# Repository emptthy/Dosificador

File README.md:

Este proyecto consta de una base de varillas y rulemanes, que servirán como soporte para una jeringa, la cual contendrá el líquido que queramos inyectar, para luego ser empujada por un motor paso a paso al marcar en un teclado la cantidad de la dosis solicitada.

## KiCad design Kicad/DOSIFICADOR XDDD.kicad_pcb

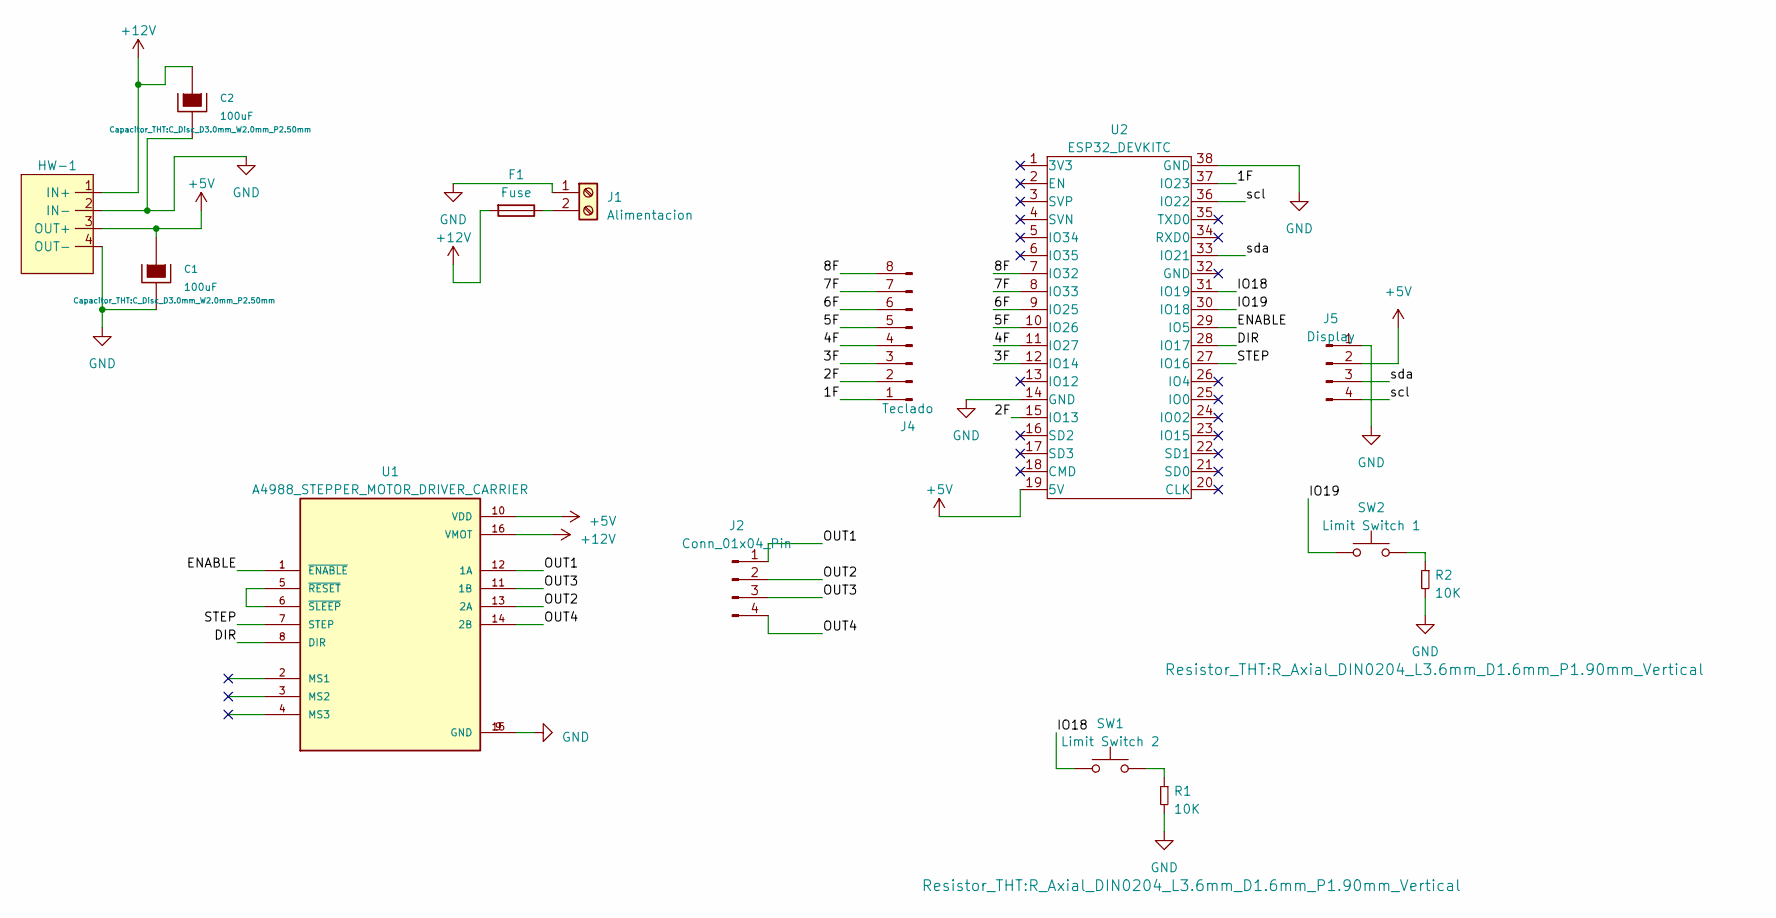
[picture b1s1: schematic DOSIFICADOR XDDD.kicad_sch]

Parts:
C1, C2: 100uF; C_Disc_D3.0mm_W2.0mm_P2.50mm
F1: Fuse; Fuse_Bourns_MF-RG300
HW-1: stepdown
J1: Alimentacion; BORNERA2_AZUL
J2: Conn_01x04_Pin; PinHeader_1x04_P2.54mm_Vertical
J4: Teclado; Pin_Header_Straight_1x08
J5: Display; pin_strip_4
R1, R2: 10K; R_Axial_DIN0204_L3.6mm_D1.6mm_P1.90mm_Vertical
SW1: Limit Switch 2; PinHeader_1x02_P2.00mm_Vertical
SW2: Limit Switch 1; PinHeader_1x02_P2.00mm_Vertical
U1: A4988_STEPPER_MOTOR_DRIVER_CARRIER; MODULE_A4988_STEPPER_MOTOR_DRIVER_CARRIER
U2: ESP32_DEVKITC

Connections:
+5V: C1.1, HW-1.3 (OUT+), J5.2, U1.10 (VDD), U2.19 (5V)
+12V: C2.1, F1.2, HW-1.1 (IN+), U1.16 (VMOT)
/1F: J4.1, U2.37 (IO23)
/2F: J4.2, U2.15 (IO13)
/3F: J4.3, U2.12 (IO14)
/4F: J4.4, U2.11 (IO27)
/5F: J4.5, U2.10 (IO26)
/6F: J4.6, U2.9 (IO25)
/7F: J4.7, U2.8 (IO33)
/8F: J4.8, U2.7 (IO32)
/DIR: U1.8 (DIR), U2.28 (IO17)
/ENABLE: U1.1 (~ENABLE), U2.29 (IO5)
/IO18: SW1.1, U2.31 (IO19)
/IO19: SW2.1, U2.30 (IO18)
/OUT1: J2.1, U1.12 (1A)
/OUT2: J2.2, U1.13 (2A)
/OUT3: J2.3, U1.11 (1B)
/OUT4: J2.4, U1.14 (2B)
/STEP: U1.7 (STEP), U2.27 (IO16)
/scl: J5.4, U2.36 (IO22)
/sda: J5.3, U2.33 (IO21)
GND: C1.2, C2.2, HW-1.2 (IN-), HW-1.4 (OUT-), J1.1, J5.1, R1.2, R2.2, U1.9 (GND), U1.15 (GND), U2.14 (GND), U2.38 (GND)
unnamed: F1.1, J1.2
unnamed: R1.1, SW1.2
unnamed: R2.1, SW2.2
unnamed: U1.5 (~RESET), U1.6 (~SLEEP)

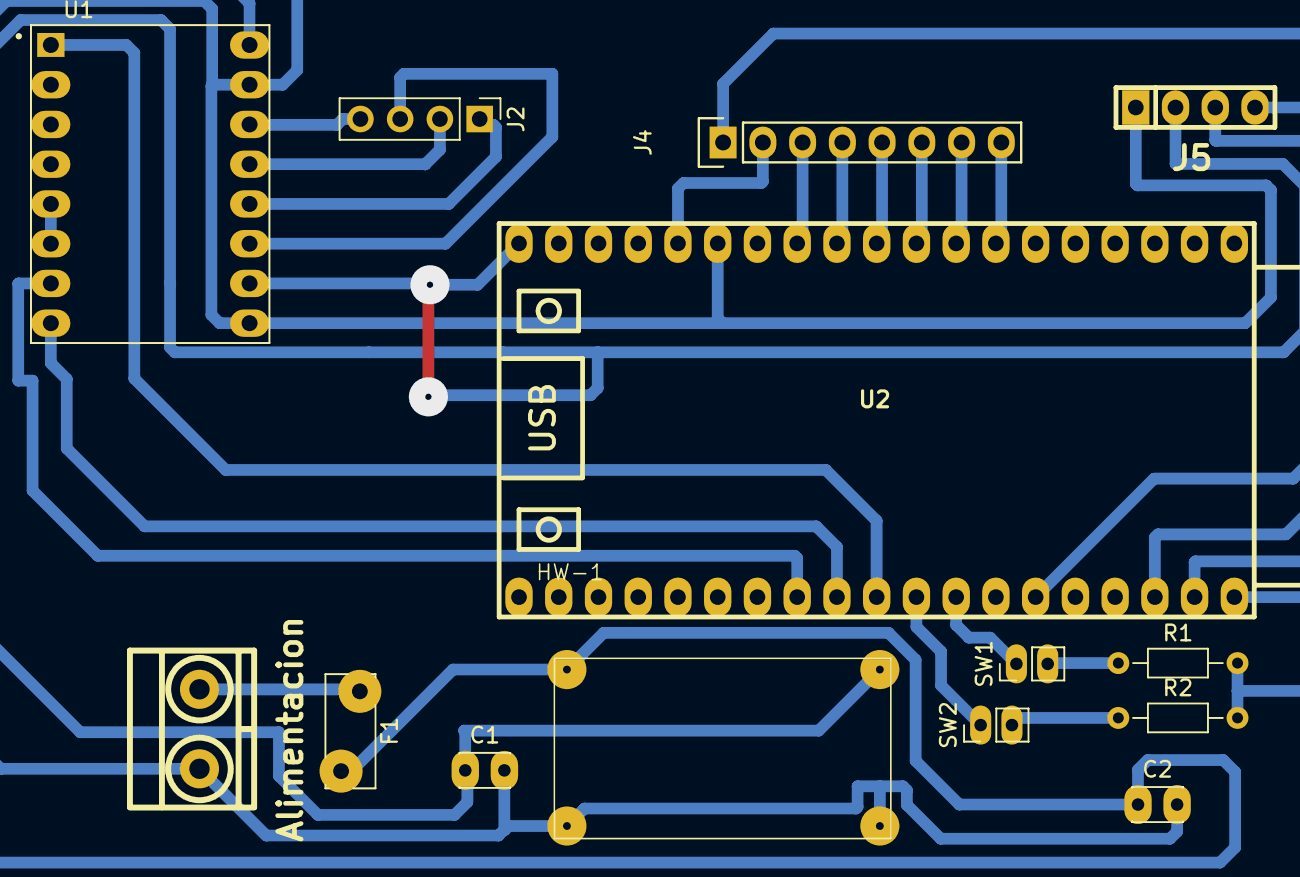
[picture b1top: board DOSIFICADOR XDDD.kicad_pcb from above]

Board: 2 copper layers, 14 parts (0 on the bottom side), 26 nets.
